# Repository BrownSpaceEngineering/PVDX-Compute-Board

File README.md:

# PVDX Compute Board

This repo contains kicad files for the PVDX Compute board, the main command/control interface for PVDX. The board contains: the SAMD51 microcontroller, 3 MRAM chips, an accelerometer, a 3-axis magnetometer, and headers for interfacing with the EPS, the battery board, the burn wire, the photodiodes, the ADCS/perovskite boards, the S-Band, the UHF, the display, and the ArduCam. 

The repo is organized into four main folders: 
1. Components (kicad symbols, footprints, and step files for each component not already built into the kicad libraries; shared between the other three folders)
2. SAMD51 Devboard (a simplified version for testing; it is run off USB-C, and houses only buck converters (not present on the final boards) and the SAMD51. All other components are exposed as headers. Every pin on the SAMD51 is also exposed)
3. Compute Board (the two layer implementation of the unified board containing all the final flight components with headers only for peripherals)
4. compute4layer (a copy of the Compute Board project with only the layout changed to a 4-layer (signal, GND, power, signal) stackup)

## Schematics 

Presented here are images of the schematics shared by the Compute Board and compute4layer: 

## Datasheets

For ease of access, here is a table of datasheets for the onboard components: 

| Component   | Part number |
| ----------- | ----------- | 
| SAMD51 | [Microchip ATSAMD51N19A](https://ww1.microchip.com/downloads/aemDocuments/documents/MCU32/ProductDocuments/DataSheets/SAM-D5x-E5x-Family-Data-Sheet-DS60001507.pdf) |
| MRAM        | [Everspin EM008LX](https://datasheet.lcsc.com/datasheet/pdf/902c3bb2baf214246dee551af985b64a.pdf?productCode=C17289052) |
| Accelerometer   | [Murata SCH16T-K01](https://sensorsandpower.angst-pfister.com/fileadmin/images/news/Datasheet-SCH16T-K01_JAN2024.pdf) |
| Magnetometer | [PNI RM3100](https://www.tri-m.com/products/pni/RM3100-User-Manual.pdf) |
| Buck converter | [Microchip MCP-1604-180I](https://ww1.microchip.com/downloads/aemDocuments/documents/OTH/ProductDocuments/DataSheets/22042B.pdf) |
| I2C Multiplexer | [TI TCA9546A](https://www.ti.com/lit/ds/symlink/tca9546a.pdf?ts=1790848067365&ref_url=https%253A%252F%252Fwww.ti.com%252Fproduct%252FTCA9546A%253Futm_source%253Dgoogle%2526utm_medium%253Dcpc%2526utm_campaign%253Dasc-tech-inno-dynpf_interface-cpc-pf-google-eu_en_int%2526utm_content%253Dprodfolddynamic%2526gclsrc%253Daw.ds%2526gad_source%253D1%2526gad_campaignid%253D23906084824%2526gbraid%253D0AAAAAC068F1EFfNekYsYivcdyWkmR2bSt%2526gclid%253DCjwKCAjwifjVBhBKEiwAYx4K9HgTKyl_4xHH1cxt9nXmtXohIvQla9mqUfnjyi_wMP_Zy_10j3Y5wxoCV-IQAvD_BwE) |

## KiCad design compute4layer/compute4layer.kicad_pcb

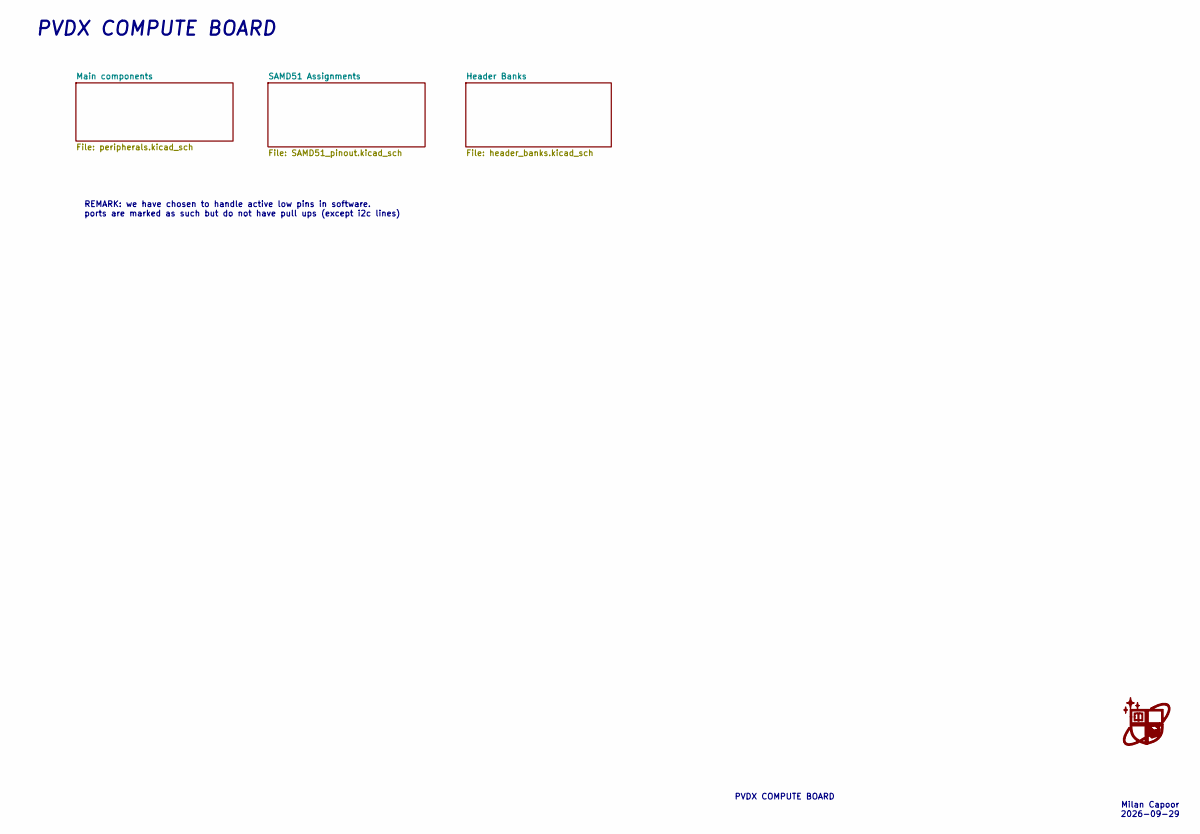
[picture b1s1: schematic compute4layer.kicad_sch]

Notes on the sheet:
REMARK: we have chosen to handle active low pins in software. ports are marked as such but do not have pull ups (except i2c lines)
Milan Capoor 2026-09-29
PVDX COMPUTE BOARD
PVDX COMPUTE BOARD

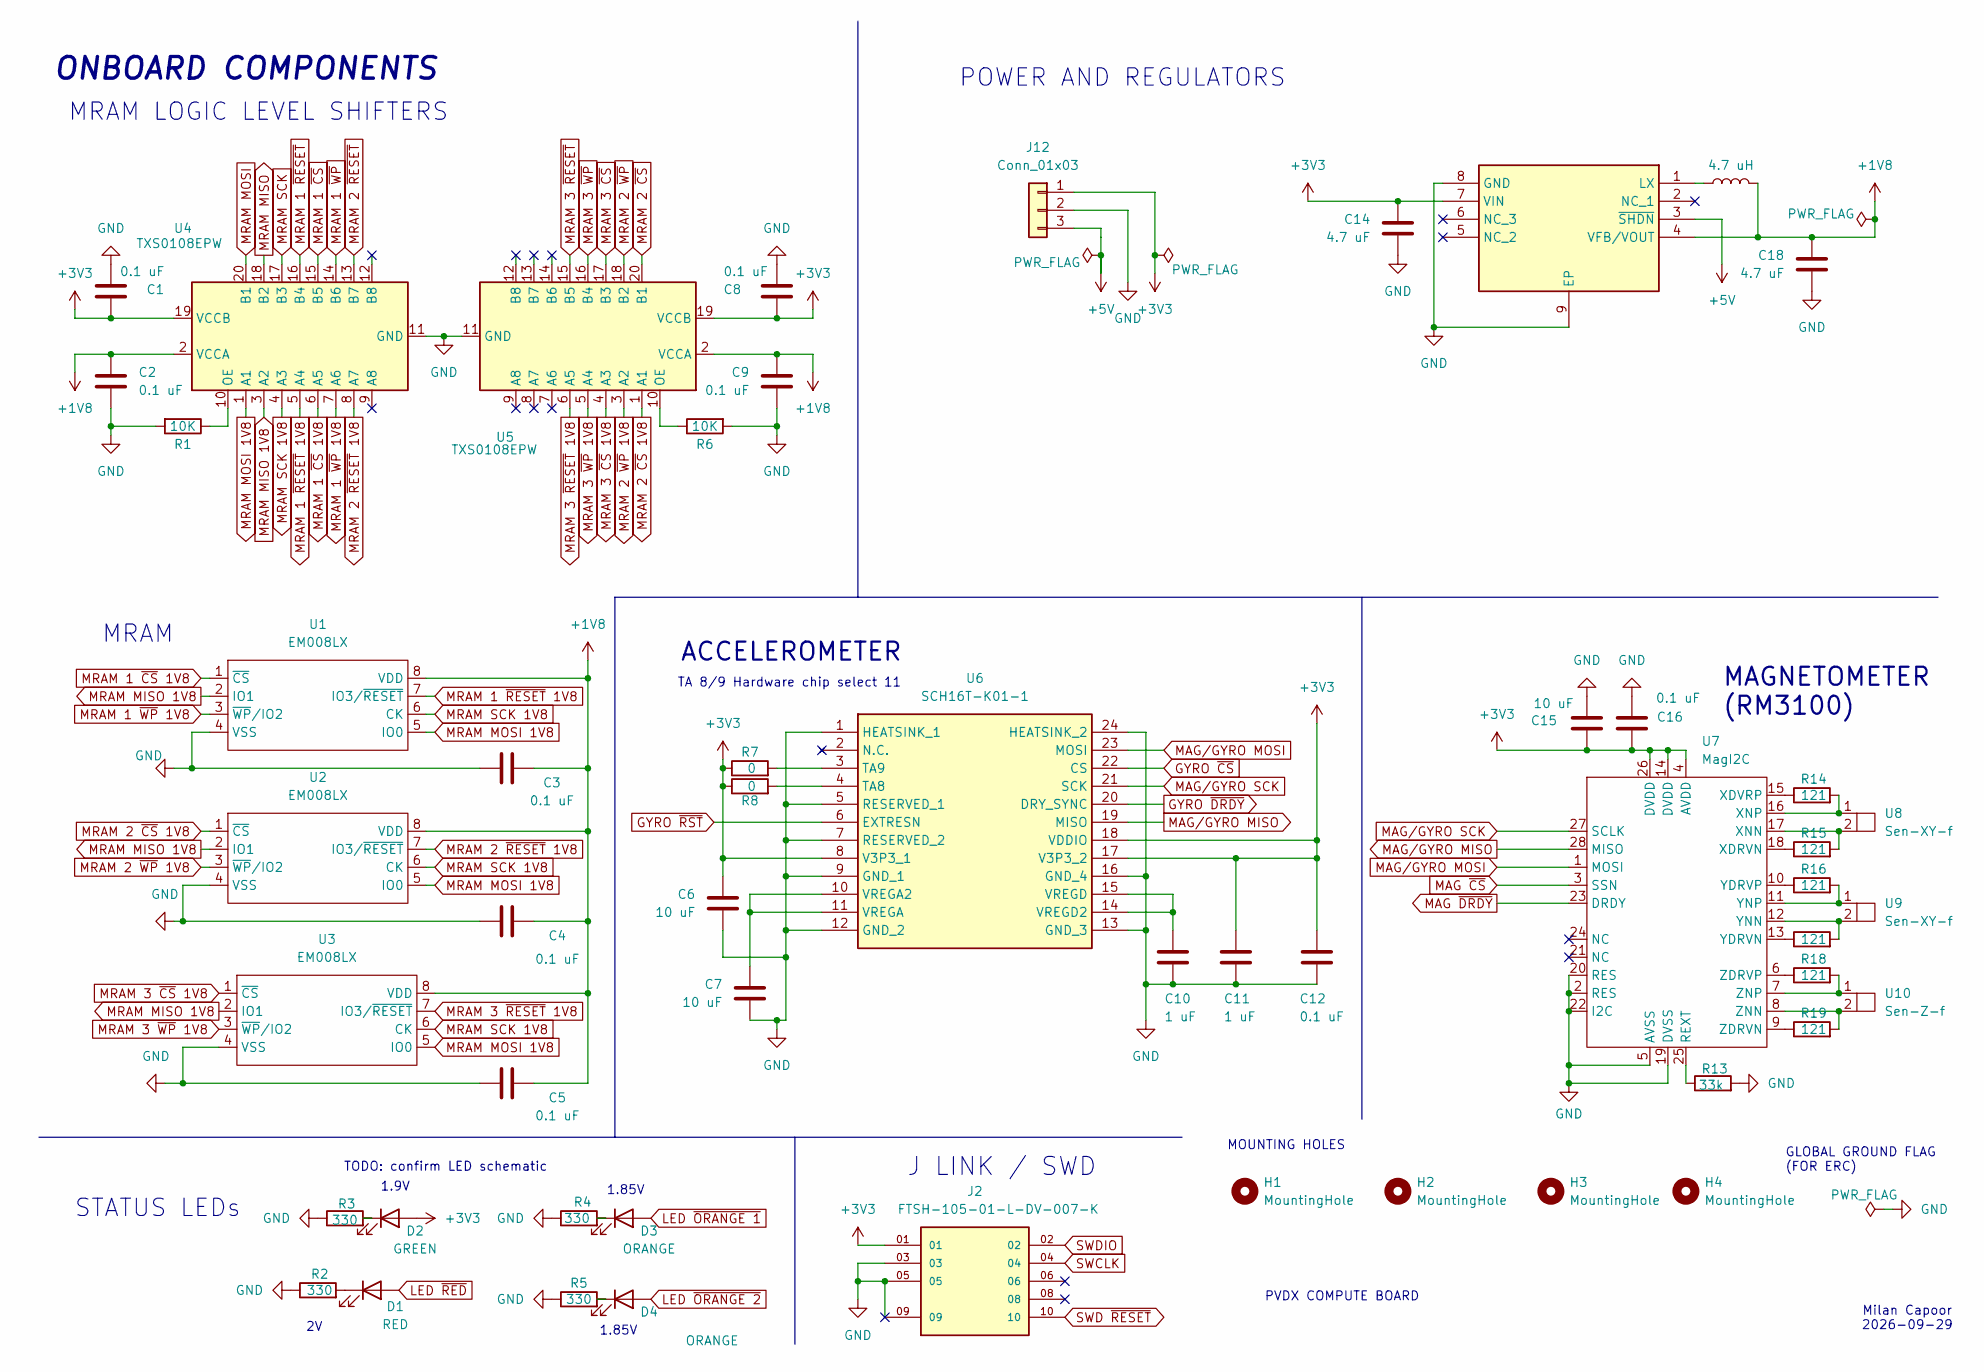
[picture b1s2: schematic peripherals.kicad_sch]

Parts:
C1, C2, C3, C4, C5, C8, C9, C12, C16: 0.1 uF; C_0603_1608Metric
C6, C7, C15: 10 uF; C_0603_1608Metric
C10, C11: 1 uF; C_0603_1608Metric
C14, C18: 4.7 uF; C_0603_1608Metric
D1: RED; LED_0603_1608Metric
D2: GREEN; LED_0603_1608Metric
D3, D4: ORANGE; LED_0603_1608Metric
H1, H2, H3, H4: MountingHole; MountingHole_3.2mm_M3
IC2: MCP1603-180I_MC; MPC1603-180; Mouser Part Number 579-MCP1603-330I/MC
J2: FTSH-105-01-L-DV-007-K; SAMTEC_FTSH-105-01-L-DV-007-K; PARTREV H
J12: Conn_01x03; PinSocket_1x03_P2.54mm_Vertical
L2: 4.7 uH; L_0603_1608Metric
R1, R6: 10K; R_0603_1608Metric
R2, R3, R4, R5: 330; R_0603_1608Metric
R7, R8: 0; R_0603_1608Metric
R13: 33k; R_0603_1608Metric
R14, R15, R16, R17, R18, R19: 121; R_0603_1608Metric
U1, U2, U3: EM008LX; EM008LXQADG13IS1T
U4, U5: TXS0108EPW; TSSOP-20_4.4x6.5mm_P0.65mm
U6: SCH16T-K01-1; SCH16TK011; Mouser Part Number 81-SCH16T-K01-1
U7: MagI2C
U8, U9: Sen-XY-f
U10: Sen-Z-f

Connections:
+1V8: C2.1, C3.2, C4.2, C5.2, C9.1, C18.1, IC2.4 (VFB/VOUT), L2.2, U1.8 (VDD), U2.8 (VDD), U3.8 (VDD), U4.2 (VCCA), U5.2 (VCCA)
+3V3: C1.1, C6.1, C8.1, C11.1, C12.1, C14.1, C15.2, C16.2, D2.2 (A), IC2.7 (VIN), J2.01, J12.1, R7.1, R8.1, U4.19 (VCCB), U5.19 (VCCB), U6.8 (V3P3_1), U6.17 (V3P3_2), U6.18 (VDDIO), U7.4 (AVDD), U7.14 (DVDD), U7.26 (DVDD); also elsewhere on the board
+5V: IC2.3 (~SHDN), J12.3; also elsewhere on the board
GND: C1.2, C2.2, C3.1, C4.1, C5.1, C6.2, C7.2, C8.2, C9.2, C10.2, C11.2, C12.2, C14.2, C15.1, C16.1, C18.2, IC2.8 (GND), IC2.9 (EP), J2.03, J2.05, J2.09, J12.2, R1.2, R2.1, R3.1, R4.1, R5.1, R6.2, R13.2, U1.4 (VSS), U2.4 (VSS), U3.4 (VSS), U4.11 (GND), U5.11 (GND), U6.1 (HEATSINK_1), U6.5 (RESERVED_1), U6.7 (RESERVED_2), U6.9 (GND_1), U6.12 (GND_2), U6.13 (GND_3), U6.16 (GND_4), U6.24 (HEATSINK_2), U7.2 (RES), U7.5 (AVSS), U7.19 (DVSS), U7.20 (RES), U7.22 (I2C); also elsewhere on the board
GYRO ~CS: U6.22 (CS); also elsewhere on the board
GYRO ~DRDY: U6.20 (DRY_SYNC); also elsewhere on the board
GYRO ~RST: U6.6 (EXTRESN); also elsewhere on the board
LED ~ORANGE 1: D3.2 (A); also elsewhere on the board
LED ~ORANGE 2: D4.2 (A); also elsewhere on the board
LED ~RED: D1.2 (A); also elsewhere on the board
MAG ~CS: U7.3 (SSN); also elsewhere on the board
MAG ~DRDY: U7.23 (DRDY); also elsewhere on the board
MAG/GYRO MISO: U6.19 (MISO), U7.28 (MISO); also elsewhere on the board
MAG/GYRO MOSI: U6.23 (MOSI), U7.1 (MOSI); also elsewhere on the board
MAG/GYRO SCK: U6.21 (SCK), U7.27 (SCLK); also elsewhere on the board
MRAM 1 ~CS: U4.15 (B5); also elsewhere on the board
MRAM 1 ~CS 1V8: U1.1 (~CS), U4.6 (A5)
MRAM 1 ~RESET: U4.16 (B4); also elsewhere on the board
MRAM 1 ~RESET 1V8: U1.7 (IO3/~RESET), U4.5 (A4)
MRAM 1 ~WP: U4.14 (B6); also elsewhere on the board
MRAM 1 ~WP 1V8: U1.3 (~WP/IO2), U4.7 (A6)
MRAM 2 ~CS: U5.20 (B1); also elsewhere on the board
MRAM 2 ~CS 1V8: U2.1 (~CS), U5.1 (A1)
MRAM 2 ~RESET: U4.13 (B7); also elsewhere on the board
MRAM 2 ~RESET 1V8: U2.7 (IO3/~RESET), U4.8 (A7)
MRAM 2 ~WP: U5.18 (B2); also elsewhere on the board
MRAM 2 ~WP 1V8: U2.3 (~WP/IO2), U5.3 (A2)
MRAM 3 ~CS: U5.17 (B3); also elsewhere on the board
MRAM 3 ~CS 1V8: U3.1 (~CS), U5.4 (A3)
MRAM 3 ~RESET: U5.15 (B5); also elsewhere on the board
MRAM 3 ~RESET 1V8: U3.7 (IO3/~RESET), U5.6 (A5)
MRAM 3 ~WP: U5.16 (B4); also elsewhere on the board
MRAM 3 ~WP 1V8: U3.3 (~WP/IO2), U5.5 (A4)
MRAM MISO: U4.18 (B2); also elsewhere on the board
MRAM MISO 1V8: U1.2 (IO1), U2.2 (IO1), U3.2 (IO1), U4.3 (A2)
MRAM MOSI: U4.20 (B1); also elsewhere on the board
MRAM MOSI 1V8: U1.5 (IO0), U2.5 (IO0), U3.5 (IO0), U4.1 (A1)
MRAM SCK: U4.17 (B3); also elsewhere on the board
MRAM SCK 1V8: U1.6 (CK), U2.6 (CK), U3.6 (CK), U4.4 (A3)
unnamed: D1.1 (K), R2.2
unnamed: D2.1 (K), R3.2
unnamed: D3.1 (K), R4.2
unnamed: D4.1 (K), R5.2
unnamed: IC2.1 (LX), L2.1
unnamed: R1.1, U4.10 (OE)
unnamed: R6.1, U5.10 (OE)
unnamed: R8.2, U6.4 (TA8)
unnamed: R7.2, U6.3 (TA9)
unnamed: C7.1, U6.10 (VREGA2), U6.11 (VREGA)
unnamed: C10.1, U6.14 (VREGD2), U6.15 (VREGD)
unnamed: R13.1, U7.25 (REXT)
unnamed: R15.1, U7.18 (XDRVN)
unnamed: R14.1, U7.15 (XDVRP)
unnamed: R15.2, U7.17 (XNN), U8.2
unnamed: R14.2, U7.16 (XNP), U8.1
unnamed: R17.1, U7.13 (YDRVN)
unnamed: R16.1, U7.10 (YDRVP)
unnamed: R17.2, U7.12 (YNN), U9.2
unnamed: R16.2, U7.11 (YNP), U9.1
unnamed: R19.1, U7.9 (ZDRVN)
unnamed: R18.1, U7.6 (ZDRVP)
unnamed: R19.2, U7.8 (ZNN), U10.2
unnamed: R18.2, U7.7 (ZNP), U10.1
SWCLK: J2.04; also elsewhere on the board
SWD ~RESET: J2.10; also elsewhere on the board
SWDIO: J2.02; also elsewhere on the board

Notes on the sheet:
POWER AND REGULATORS
MAGNETOMETER (RM3100)
STATUS LEDs
ACCELEROMETER
ONBOARD COMPONENTS
GLOBAL GROUND FLAG (FOR ERC)
1.85V
MRAM LOGIC LEVEL SHIFTERS
J LINK / SWD
MOUNTING HOLES
PVDX COMPUTE BOARD
1.9V
TA 8/9 Hardware chip select 11
TODO: confirm LED schematic
Milan Capoor 2026-09-29
MRAM

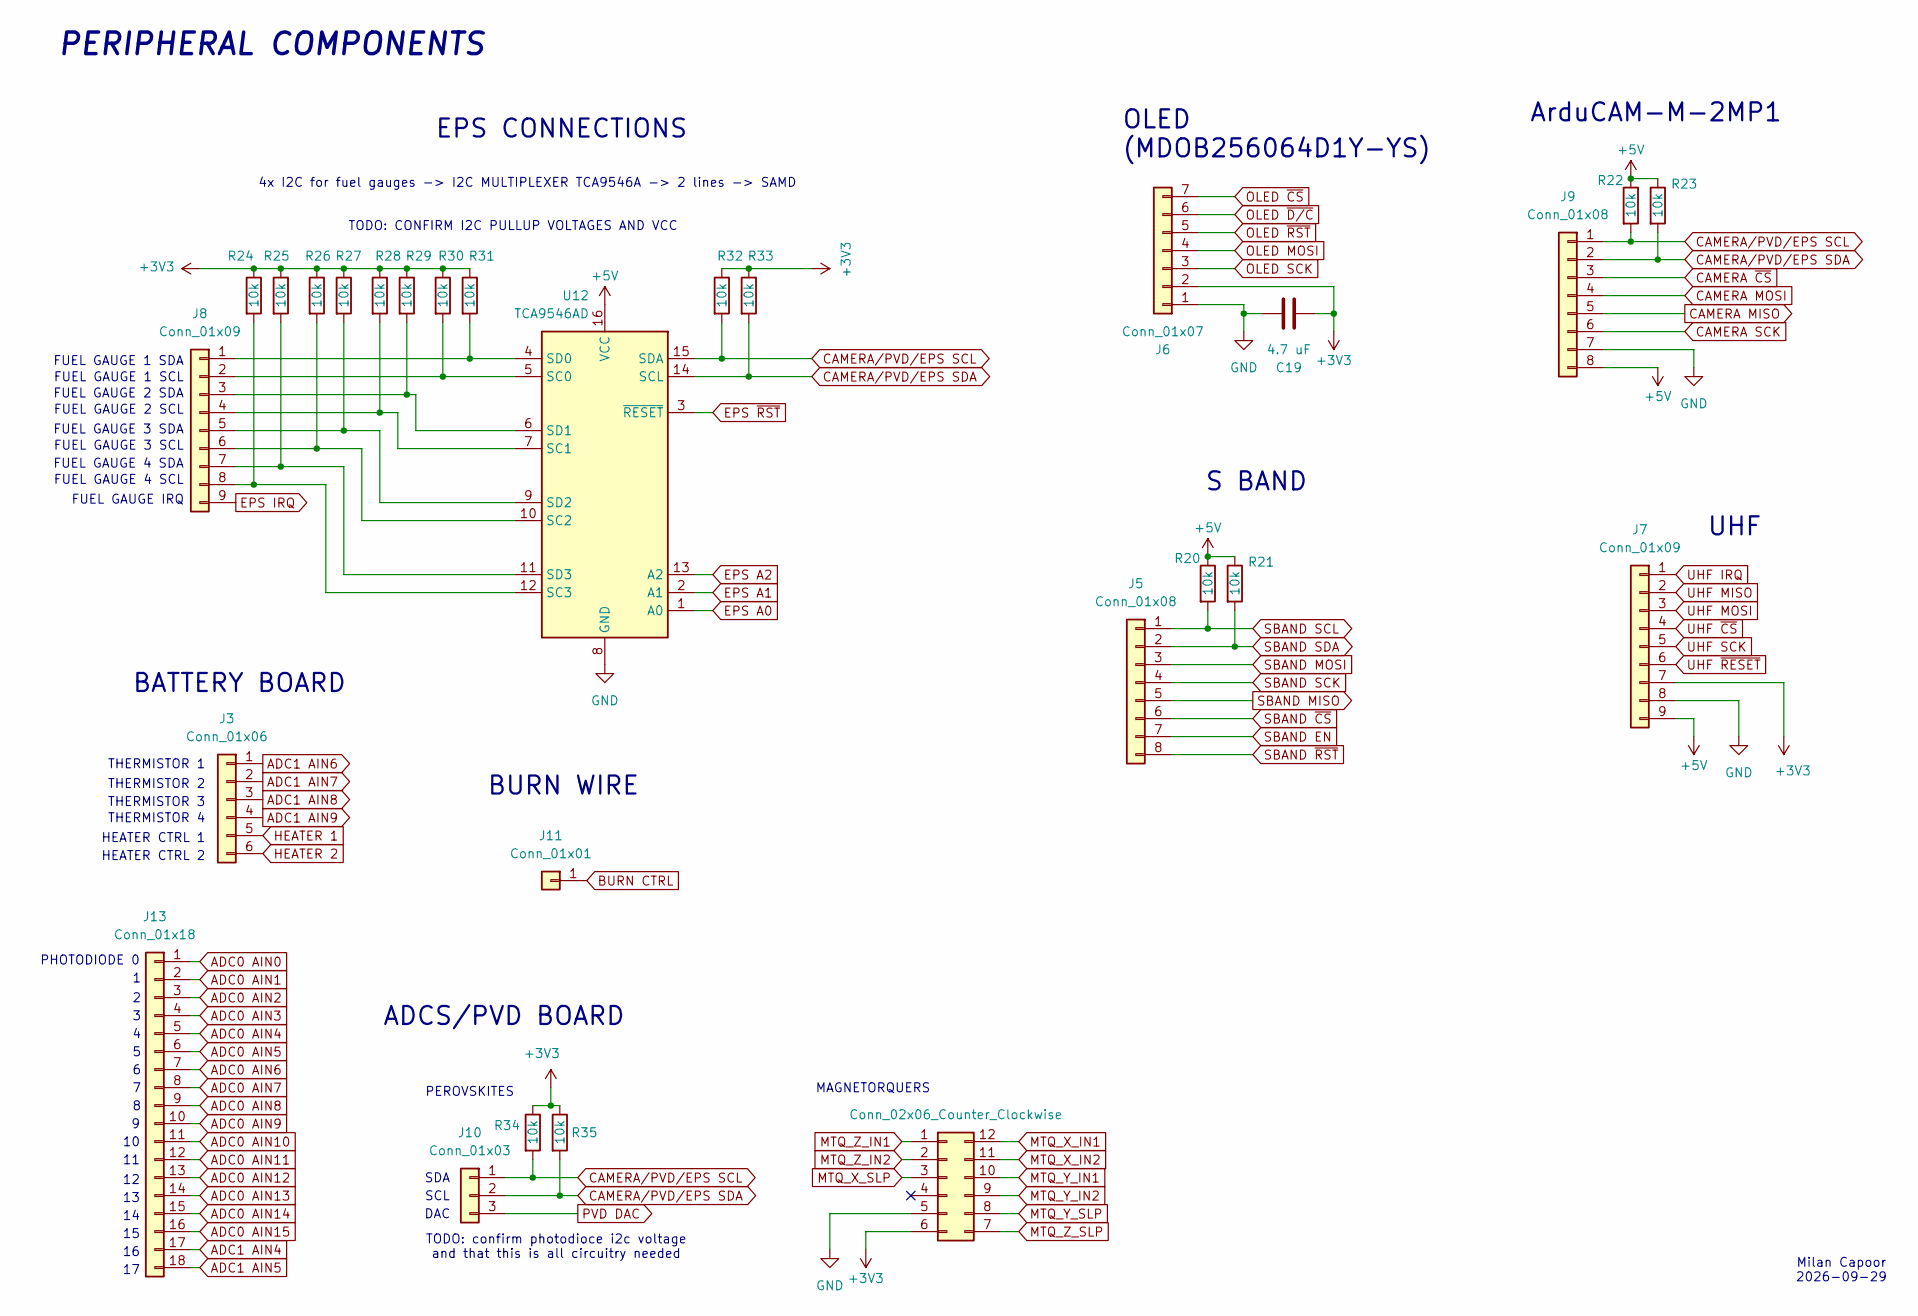
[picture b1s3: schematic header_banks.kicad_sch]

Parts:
C19: 4.7 uF; C_0603_1608Metric
J3: Conn_01x06; PinSocket_1x06_P2.54mm_Vertical
J4: Conn_02x06_Counter_Clockwise; PinSocket_2x06_P2.54mm_Vertical
J5, J9: Conn_01x08; PinSocket_1x08_P2.54mm_Vertical
J6: Conn_01x07; PinSocket_1x07_P2.54mm_Vertical
J7, J8: Conn_01x09; PinSocket_1x09_P2.54mm_Vertical
J10: Conn_01x03; PinSocket_1x03_P2.54mm_Vertical
J11: Conn_01x01; PinSocket_1x01_P2.54mm_Vertical
J13: Conn_01x18; FH34SRJ18S05SH50
R20, R21, R22, R23, R24, R25, R26, R27, R28, R29, R30, R31, R32, R33, R34, R35: 10k; R_0603_1608Metric
U12: TCA9546AD; SOIC-16_3.9x9.9mm_P1.27mm

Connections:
+3V3: C19.2, J4.6, J6.2, J7.7, R24.1, R25.1, R26.1, R27.1, R28.1, R29.1, R30.1, R31.1, R32.1, R33.1, R34.1, R35.1; also elsewhere on the board
+5V: J7.9, J9.8, R20.1, R21.1, R22.1, R23.1, U12.16 (VCC); also elsewhere on the board
ADC0 AIN0: J13.1; also elsewhere on the board
ADC0 AIN1: J13.2; also elsewhere on the board
ADC0 AIN2: J13.3; also elsewhere on the board
ADC0 AIN3: J13.4; also elsewhere on the board
ADC0 AIN4: J13.5; also elsewhere on the board
ADC0 AIN5: J13.6; also elsewhere on the board
ADC0 AIN6: J13.7; also elsewhere on the board
ADC0 AIN7: J13.8; also elsewhere on the board
ADC0 AIN8: J13.9; also elsewhere on the board
ADC0 AIN9: J13.10; also elsewhere on the board
ADC0 AIN10: J13.11; also elsewhere on the board
ADC0 AIN11: J13.12; also elsewhere on the board
ADC0 AIN12: J13.13; also elsewhere on the board
ADC0 AIN13: J13.14; also elsewhere on the board
ADC0 AIN14: J13.15; also elsewhere on the board
ADC0 AIN15: J13.16; also elsewhere on the board
ADC1 AIN4: J13.17; also elsewhere on the board
ADC1 AIN5: J13.18; also elsewhere on the board
ADC1 AIN6: J3.1; also elsewhere on the board
ADC1 AIN7: J3.2; also elsewhere on the board
ADC1 AIN8: J3.3; also elsewhere on the board
ADC1 AIN9: J3.4; also elsewhere on the board
BURN CTRL: J11.1 (Pin_1_1); also elsewhere on the board
CAMERA MISO: J9.5; also elsewhere on the board
CAMERA MOSI: J9.4; also elsewhere on the board
CAMERA SCK: J9.6; also elsewhere on the board
CAMERA ~CS: J9.3; also elsewhere on the board
CAMERA/PVD/EPS SCL: J9.1, J10.1, R22.2, R32.2, R34.2, U12.15 (SDA); also elsewhere on the board
CAMERA/PVD/EPS SDA: J9.2, J10.2, R23.2, R33.2, R35.2, U12.14 (SCL); also elsewhere on the board
EPS A0: U12.1 (A0); also elsewhere on the board
EPS A1: U12.2 (A1); also elsewhere on the board
EPS A2: U12.13 (A2); also elsewhere on the board
EPS IRQ: J8.9; also elsewhere on the board
EPS ~RST: U12.3 (~RESET); also elsewhere on the board
GND: C19.1, J4.5, J6.1, J7.8, J9.7, U12.8 (GND); also elsewhere on the board
HEATER 1: J3.5; also elsewhere on the board
HEATER 2: J3.6; also elsewhere on the board
MTQ_X_IN1: J4.12; also elsewhere on the board
MTQ_X_IN2: J4.11; also elsewhere on the board
MTQ_X_SLP: J4.3; also elsewhere on the board
MTQ_Y_IN1: J4.10; also elsewhere on the board
MTQ_Y_IN2: J4.9; also elsewhere on the board
MTQ_Y_SLP: J4.8; also elsewhere on the board
MTQ_Z_IN1: J4.1; also elsewhere on the board
MTQ_Z_IN2: J4.2; also elsewhere on the board
MTQ_Z_SLP: J4.7; also elsewhere on the board
unnamed: J8.1, R31.2, U12.4 (SD0)
unnamed: J8.2, R30.2, U12.5 (SC0)
unnamed: J8.3, R29.2, U12.6 (SD1)
unnamed: J8.4, R28.2, U12.7 (SC1)
unnamed: J8.5, R27.2, U12.9 (SD2)
unnamed: J8.6, R26.2, U12.10 (SC2)
unnamed: J8.7, R25.2, U12.11 (SD3)
unnamed: J8.8, R24.2, U12.12 (SC3)
OLED MOSI: J6.4; also elsewhere on the board
OLED SCK: J6.3; also elsewhere on the board
OLED ~CS: J6.7; also elsewhere on the board
OLED ~D/C: J6.6; also elsewhere on the board
OLED ~RST: J6.5; also elsewhere on the board
PVD DAC: J10.3; also elsewhere on the board
SBAND EN: J5.7; also elsewhere on the board
SBAND MISO: J5.5; also elsewhere on the board
SBAND MOSI: J5.3; also elsewhere on the board
SBAND SCK: J5.4; also elsewhere on the board
SBAND SCL: J5.1, R20.2; also elsewhere on the board
SBAND SDA: J5.2, R21.2; also elsewhere on the board
SBAND ~CS: J5.6; also elsewhere on the board
SBAND ~RST: J5.8; also elsewhere on the board
UHF IRQ: J7.1; also elsewhere on the board
UHF MISO: J7.2; also elsewhere on the board
UHF MOSI: J7.3; also elsewhere on the board
UHF SCK: J7.5; also elsewhere on the board
UHF ~CS: J7.4; also elsewhere on the board
UHF ~RESET: J7.6; also elsewhere on the board

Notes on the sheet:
MAGNETORQUERS
TODO: confirm photodioce i2c voltage and that this is all circuitry needed
BURN WIRE
FUEL GAUGE 2 SCL
THERMISTOR 3
PERIPHERAL COMPONENTS
OLED (MDOB256064D1Y-YS)
THERMISTOR 4
PHOTODIODE 0
EPS CONNECTIONS
HEATER CTRL 1
SDA
FUEL GAUGE 3 SDA
FUEL GAUGE 1 SDA
4x I2C for fuel gauges -> I2C MULTIPLEXER TCA9546A -> 2 lines -> SAMD
ADCS/PVD BOARD
FUEL GAUGE IRQ
THERMISTOR 2
ArduCAM-M-2MP1
DAC
HEATER CTRL 2
BATTERY BOARD
FUEL GAUGE 1 SCL
UHF
TODO: CONFIRM I2C PULLUP VOLTAGES AND VCC
Milan Capoor 2026-09-29
FUEL GAUGE 4 SCL
THERMISTOR 1
FUEL GAUGE 3 SCL
SCL
PEROVSKITES
S BAND
FUEL GAUGE 4 SDA
FUEL GAUGE 2 SDA

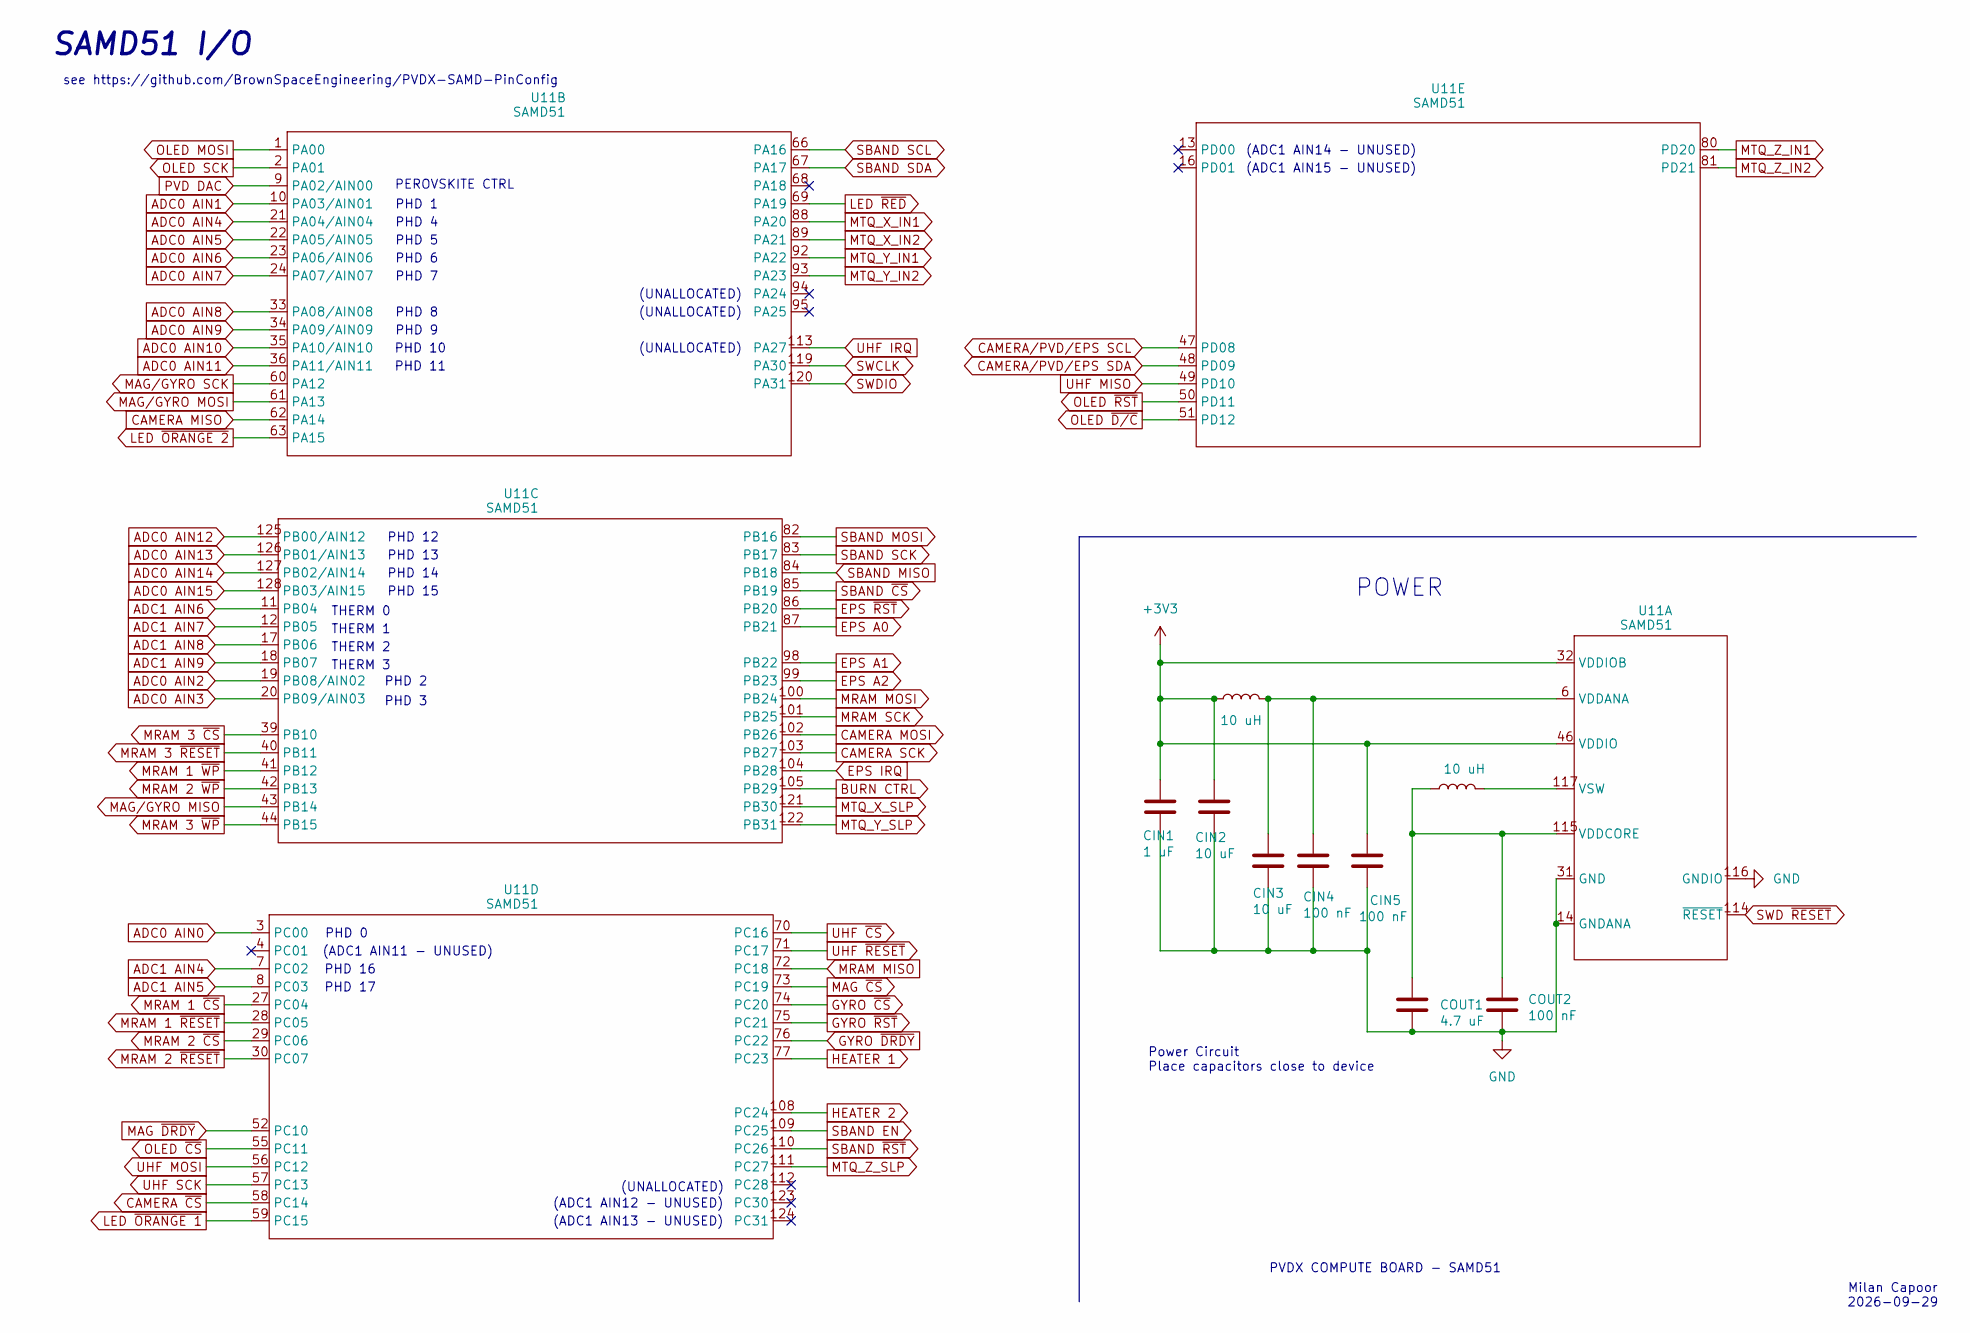
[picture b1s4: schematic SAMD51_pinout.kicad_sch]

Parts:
CIN1: 1 uF; C_0603_1608Metric
CIN2, CIN3: 10 uF; C_0603_1608Metric
CIN4, CIN5: 100 nF; C_0603_1608Metric
COUT1: 4.7 uF; C_0603_1608Metric
COUT2: 100 nF; C_0603_1608Metric
L3, L4: 10 uH; L_0603_1608Metric
U11: SAMD51; TQFP128_14X14MC_MCH-L

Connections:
+3V3: CIN1.1, CIN2.1, CIN5.1, L3.1, U11.32 (VDDIOB), U11.37 (VDDIOB), U11.46 (VDDIO), U11.54 (VDDIO), U11.65 (VDDIO), U11.79 (VDDIO), U11.91 (VDDIO), U11.97 (VDDIO), U11.107 (VDDIO), U11.118 (VDDIO); also elsewhere on the board
ADC0 AIN0: U11.3 (PC00); also elsewhere on the board
ADC0 AIN1: U11.10 (PA03/AIN01); also elsewhere on the board
ADC0 AIN2: U11.19 (PB08/AIN02); also elsewhere on the board
ADC0 AIN3: U11.20 (PB09/AIN03); also elsewhere on the board
ADC0 AIN4: U11.21 (PA04/AIN04); also elsewhere on the board
ADC0 AIN5: U11.22 (PA05/AIN05); also elsewhere on the board
ADC0 AIN6: U11.23 (PA06/AIN06); also elsewhere on the board
ADC0 AIN7: U11.24 (PA07/AIN07); also elsewhere on the board
ADC0 AIN8: U11.33 (PA08/AIN08); also elsewhere on the board
ADC0 AIN9: U11.34 (PA09/AIN09); also elsewhere on the board
ADC0 AIN10: U11.35 (PA10/AIN10); also elsewhere on the board
ADC0 AIN11: U11.36 (PA11/AIN11); also elsewhere on the board
ADC0 AIN12: U11.125 (PB00/AIN12); also elsewhere on the board
ADC0 AIN13: U11.126 (PB01/AIN13); also elsewhere on the board
ADC0 AIN14: U11.127 (PB02/AIN14); also elsewhere on the board
ADC0 AIN15: U11.128 (PB03/AIN15); also elsewhere on the board
ADC1 AIN4: U11.7 (PC02); also elsewhere on the board
ADC1 AIN5: U11.8 (PC03); also elsewhere on the board
ADC1 AIN6: U11.11 (PB04); also elsewhere on the board
ADC1 AIN7: U11.12 (PB05); also elsewhere on the board
ADC1 AIN8: U11.17 (PB06); also elsewhere on the board
ADC1 AIN9: U11.18 (PB07); also elsewhere on the board
BURN CTRL: U11.105 (PB29); also elsewhere on the board
CAMERA MISO: U11.62 (PA14); also elsewhere on the board
CAMERA MOSI: U11.102 (PB26); also elsewhere on the board
CAMERA SCK: U11.103 (PB27); also elsewhere on the board
CAMERA ~CS: U11.58 (PC14); also elsewhere on the board
CAMERA/PVD/EPS SCL: U11.47 (PD08); also elsewhere on the board
CAMERA/PVD/EPS SDA: U11.48 (PD09); also elsewhere on the board
EPS A0: U11.87 (PB21); also elsewhere on the board
EPS A1: U11.98 (PB22); also elsewhere on the board
EPS A2: U11.99 (PB23); also elsewhere on the board
EPS IRQ: U11.104 (PB28); also elsewhere on the board
EPS ~RST: U11.86 (PB20); also elsewhere on the board
GND: CIN1.2, CIN2.2, CIN3.2, CIN4.2, CIN5.2, COUT1.2, COUT2.2, U11.5 (GND), U11.14 (GNDANA), U11.25 (GNDANA), U11.31 (GND), U11.38 (GND), U11.45 (GND), U11.53 (GND), U11.64 (GND), U11.78 (GND), U11.90 (GND), U11.96 (GND), U11.106 (GND), U11.116 (GNDIO); also elsewhere on the board
GYRO ~CS: U11.74 (PC20); also elsewhere on the board
GYRO ~DRDY: U11.76 (PC22); also elsewhere on the board
GYRO ~RST: U11.75 (PC21); also elsewhere on the board
HEATER 1: U11.77 (PC23); also elsewhere on the board
HEATER 2: U11.108 (PC24); also elsewhere on the board
LED ~ORANGE 1: U11.59 (PC15); also elsewhere on the board
LED ~ORANGE 2: U11.63 (PA15); also elsewhere on the board
LED ~RED: U11.69 (PA19); also elsewhere on the board
MAG ~CS: U11.73 (PC19); also elsewhere on the board
MAG ~DRDY: U11.52 (PC10); also elsewhere on the board
MAG/GYRO MISO: U11.43 (PB14); also elsewhere on the board
MAG/GYRO MOSI: U11.61 (PA13); also elsewhere on the board
MAG/GYRO SCK: U11.60 (PA12); also elsewhere on the board
MRAM 1 ~CS: U11.27 (PC04); also elsewhere on the board
MRAM 1 ~RESET: U11.28 (PC05); also elsewhere on the board
MRAM 1 ~WP: U11.41 (PB12); also elsewhere on the board
MRAM 2 ~CS: U11.29 (PC06); also elsewhere on the board
MRAM 2 ~RESET: U11.30 (PC07); also elsewhere on the board
MRAM 2 ~WP: U11.42 (PB13); also elsewhere on the board
MRAM 3 ~CS: U11.39 (PB10); also elsewhere on the board
MRAM 3 ~RESET: U11.40 (PB11); also elsewhere on the board
MRAM 3 ~WP: U11.44 (PB15); also elsewhere on the board
MRAM MISO: U11.72 (PC18); also elsewhere on the board
MRAM MOSI: U11.100 (PB24); also elsewhere on the board
MRAM SCK: U11.101 (PB25); also elsewhere on the board
MTQ_X_IN1: U11.88 (PA20); also elsewhere on the board
MTQ_X_IN2: U11.89 (PA21); also elsewhere on the board
MTQ_X_SLP: U11.121 (PB30); also elsewhere on the board
MTQ_Y_IN1: U11.92 (PA22); also elsewhere on the board
MTQ_Y_IN2: U11.93 (PA23); also elsewhere on the board
MTQ_Y_SLP: U11.122 (PB31); also elsewhere on the board
MTQ_Z_IN1: U11.80 (PD20); also elsewhere on the board
MTQ_Z_IN2: U11.81 (PD21); also elsewhere on the board
MTQ_Z_SLP: U11.111 (PC27); also elsewhere on the board
unnamed: COUT1.1, COUT2.1, L4.1, U11.115 (VDDCORE)
unnamed: L4.2, U11.117 (VSW)
OLED MOSI: U11.1 (PA00); also elsewhere on the board
OLED SCK: U11.2 (PA01); also elsewhere on the board
OLED ~CS: U11.55 (PC11); also elsewhere on the board
OLED ~D/C: U11.51 (PD12); also elsewhere on the board
OLED ~RST: U11.50 (PD11); also elsewhere on the board
PVD DAC: U11.9 (PA02/AIN00); also elsewhere on the board
SBAND EN: U11.109 (PC25); also elsewhere on the board
SBAND MISO: U11.84 (PB18); also elsewhere on the board
SBAND MOSI: U11.82 (PB16); also elsewhere on the board
SBAND SCK: U11.83 (PB17); also elsewhere on the board
SBAND SCL: U11.66 (PA16); also elsewhere on the board
SBAND SDA: U11.67 (PA17); also elsewhere on the board
SBAND ~CS: U11.85 (PB19); also elsewhere on the board
SBAND ~RST: U11.110 (PC26); also elsewhere on the board
SWCLK: U11.119 (PA30); also elsewhere on the board
SWD ~RESET: U11.114 (~RESET); also elsewhere on the board
SWDIO: U11.120 (PA31); also elsewhere on the board
UHF IRQ: U11.113 (PA27); also elsewhere on the board
UHF MISO: U11.49 (PD10); also elsewhere on the board
UHF MOSI: U11.56 (PC12); also elsewhere on the board
UHF SCK: U11.57 (PC13); also elsewhere on the board
UHF ~CS: U11.70 (PC16); also elsewhere on the board
UHF ~RESET: U11.71 (PC17); also elsewhere on the board
VDDANA: CIN3.1, CIN4.1, L3.2, U11.6 (VDDANA), U11.15 (VDDANA), U11.26 (VDDANA)

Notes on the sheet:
THERM 1
PHD 2
see https://github.com/BrownSpaceEngineering/PVDX-SAMD-PinConfig
PHD 8
THERM 2
(ADC1 AIN12 - UNUSED)
PHD 14
PHD 15
Power Circuit Place capacitors close to device
PHD 6
THERM 0
PHD 1
(UNALLOCATED)
PHD 17
PHD 7
(ADC1 AIN15 - UNUSED)
PHD 9
POWER
(ADC1 AIN14 - UNUSED)
PHD 12
PHD 11
PHD 3
PHD 5
PHD 0
PHD 13
(ADC1 AIN11 - UNUSED)
Milan Capoor 2026-09-29
(ADC1 AIN13 - UNUSED)
SAMD51 I/O
PHD 16
PHD 10
PEROVSKITE CTRL
PHD 4
THERM 3
PVDX COMPUTE BOARD - SAMD51

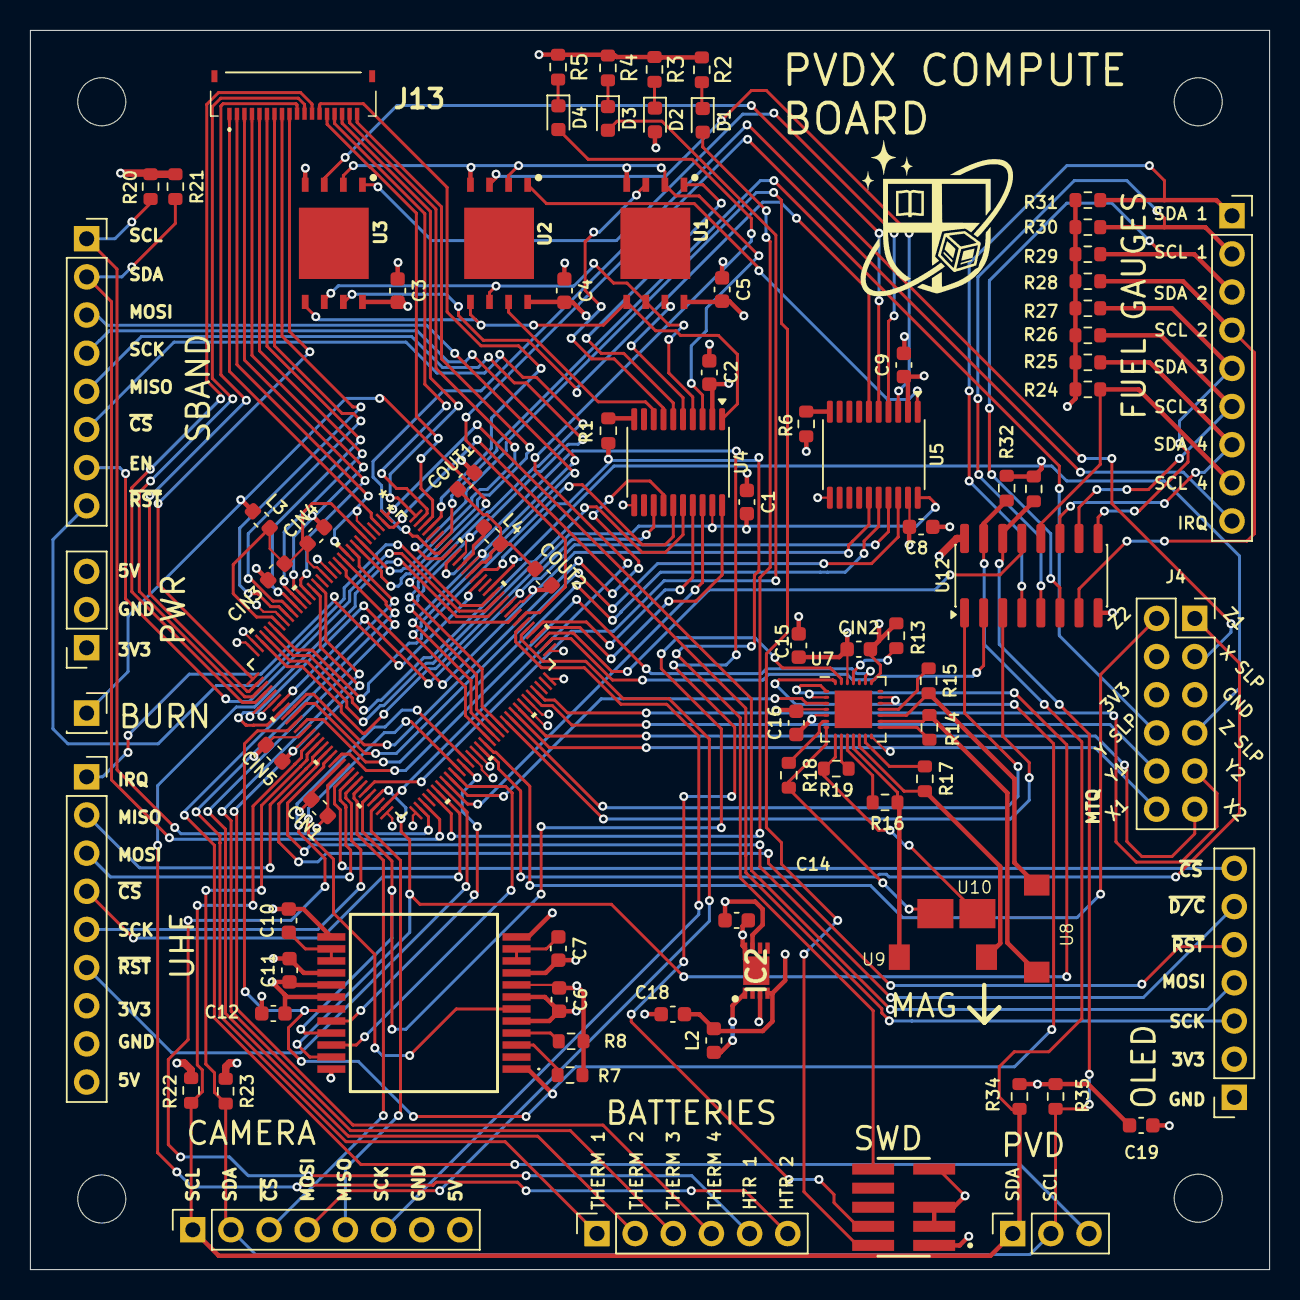
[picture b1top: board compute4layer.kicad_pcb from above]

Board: 4 copper layers, 82.5 x 82.5 mm, 91 parts (0 on the bottom side), 142 nets.
